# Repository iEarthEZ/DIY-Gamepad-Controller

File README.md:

# DIY-Gamepad-Controller
Making a custom gamepad controller from scratch. {I'll update code files and firmware when my parts get shipped.}.

Lets walk you through here from where i got the idea to where we are now. First things first the idea came to my mind because not too long ago i bought my cool red ps4 controller so i thought "what if i could make something like this myself?". Thats what it hit me, i was like I can make that so i got to work on the research my brother was making a split keyboard and he used the arduino pro micro mini as the "brain" or main chip. He said if you are making something like that use the pro micro mini so i atlast settled down with the normal usb-c version of the pro micro(the mini's pins are abit different). If you are making this project like me i recommend the video https://www.youtube.com/watch?v=mvv1BRjswew by Voltaat. It will get you started with ide and programming so it'll be easy and i recommend watching some soldering tutorials lol. Also first things first you should download all the project files and open them up in kicad and check it out or edit stuff yourself!(feel free). If you goto the pcb section and press alt + 3 you can see a base model of how it will look(its the reference image at the start of this readme). Its straight forward, upload gerber files to jlcpcb or pcbway or anyother you like i guess, wait for the pcb to get shipped to you, order the given parts in the BOM and just assemble them. Thats it! I made the controller a basic comfortable shape but you can make it any shape you like. If you know the basics of kicad i don't think it will be a pain to get through everything. It was my second ever pcb and project with kicad and stuff so i was pretty scared but at the end i found out it ain't hard. Looking forward to everyone that makes this project and in the next upd i'll drop all the firmware and code files even a tutorial on how to code the ide after my parts gets shipped. Till then. Peace.

HERE IS THE BOM!!!!! (NOTE THAT ALL OF THIS IS FROM MY INSIDE COUNTRY'S WEBSITES YOU CAN JUST SEARCH FOR THE PART NAMES AND GET THEM FROM YOUR LOCAL SHOP OR LOCAL WEBSITE)

|Name                                                                                                                                                                  |Purpose                                                                            |Quantity|Total Cost (USD)|Link                                                                                                                                                                                                                                                                                                                                                                                                                                                                                                                                                                                                                                                                                                                                                                                                                                                                                                                                                                                                                                                                                                   |Distributor|
|----------------------------------------------------------------------------------------------------------------------------------------------------------------------|-----------------------------------------------------------------------------------|--------|----------------|-------------------------------------------------------------------------------------------------------------------------------------------------------------------------------------------------------------------------------------------------------------------------------------------------------------------------------------------------------------------------------------------------------------------------------------------------------------------------------------------------------------------------------------------------------------------------------------------------------------------------------------------------------------------------------------------------------------------------------------------------------------------------------------------------------------------------------------------------------------------------------------------------------------------------------------------------------------------------------------------------------------------------------------------------------------------------------------------------------|-----------|
|Joystick Dual Axis 5 Pin Breakout Module For Arduino                                                                                                                  |Joysticks for the controller                                                       |2       |1.61            |https://www.bdtronics.com/joystick-dual-axis-5-pin-breakout-module-for-arduino.html                                                                                                                                                                                                                                                                                                                                                                                                                                                                                                                                                                                                                                                                                                                                                                                                                                                                                                                                                                                                                    |BDTronics  |
|10Pcs- RIGHT Angle Momentary 2Pin Tactile Tact Push Button Switches 2 Pin 6x6x7mm 90 Degree Bend On Off PCB DIP Through Hole Touch Switch Momentary Push Button Switch|right angled buttons for the shoulder and triggers                                 |1       |0.76            |https://www.daraz.com.bd/products/10-2-2-6x6x7mm-90-pcb-i129768178-s1049544950.html?c=&channelLpJumpArgs=&clickTrackInfo=query%253Aangled%252Bpush%252Bbutton%253Bnid%253A129768178%253Bsrc%253ALazadaMainSrp%253Brn%253A0ec6cdb791f19f113f57f372a77d82df%253Bregion%253Abd%253Bsku%253A129768178_BD%253Bprice%253A93%253Bclient%253Adesktop%253Bsupplier_id%253A1000750%253Bsession_id%253A%253Bbiz_source%253Ah5_external%253Bslot%253A13%253Butlog_bucket_id%253A470687%253Basc_category_id%253A10000486%253Bitem_id%253A129768178%253Bsku_id%253A1049544950%253Bshop_id%253A6947%253BtemplateInfo%253A&freeshipping=0&fs_ab=1&fuse_fs=&lang=en&location=Dhaka&price=93&priceCompare=skuId%3A1049544950%3Bsource%3Alazada-search-voucher%3Bsn%3A0ec6cdb791f19f113f57f372a77d82df%3BoriginPrice%3A9300%3BdisplayPrice%3A9300%3BsinglePromotionId%3A-1%3BsingleToolCode%3AmockedSalePrice%3BvoucherPricePlugin%3A0%3Btimestamp%3A1777640799160&ratingscore=4.666666666666667&request_id=0ec6cdb791f19f113f57f372a77d82df&review=15&sale=70&search=1&source=search&spm=a2a0e.searchlist.list.13&stock=1|DarazBD    |
|Mini Push Button Tactile Switch 4 Pin (6mm*6mm*4.5mm)                                                                                                                 |buttons of the controller                                                          |10      |0.41            |https://www.bdtronics.com/mini-push-button-tactile-switch-4-pin-6mm-6mm-4-5mm.html                                                                                                                                                                                                                                                                                                                                                                                                                                                                                                                                                                                                                                                                                                                                                                                                                                                                                                                                                                                                                     |BDTronics  |
|1/4 Resistor                                                                                                                                                          |resistor so the led doesn't burn out                                               |1       |0.02            |https://www.bdtronics.com/carbon-film-1-4w-resistor.html                                                                                                                                                                                                                                                                                                                                                                                                                                                                                                                                                                                                                                                                                                                                                                                                                                                                                                                                                                                                                                               |BDTronics  |
|WHITE LED                                                                                                                                                             |showing connection status of the controller and white led on black pcb is just good|1       |0.02            |https://www.bdtronics.com/3mm-led-red-green-blue-yellow-white.html                                                                                                                                                                                                                                                                                                                                                                                                                                                                                                                                                                                                                                                                                                                                                                                                                                                                                                                                                                                                                                     |BDTronics  |
|Arduino Pro Micro                                                                                                                                                     |the brain of this controller                                                       |1       |5.05            |https://www.bdtronics.com/arduino-pro-micro-atmega32u4-5v-16mhz.html                                                                                                                                                                                                                                                                                                                                                                                                                                                                                                                                                                                                                                                                                                                                                                                                                                                                                                                                                                                                                                   |BDTronics  |
|PCB                                                                                                                                                                   |the pcb                                                                            |1       |15.50           |https://trade.jlcpcb.com/checkout/payMethod/?unionSettleId=26dcc378283c4002b6bfed6f815bbe98&systemType=order_pcb&orderTypes=order_pcb&calType=PRE_CAL&couponDemo=1&spm=Jlcpcb.Partcart.1002                                                                                                                                                                                                                                                                                                                                                                                                                                                                                                                                                                                                                                                                                                                                                                                                                                                                                                            |JLCPCB     |

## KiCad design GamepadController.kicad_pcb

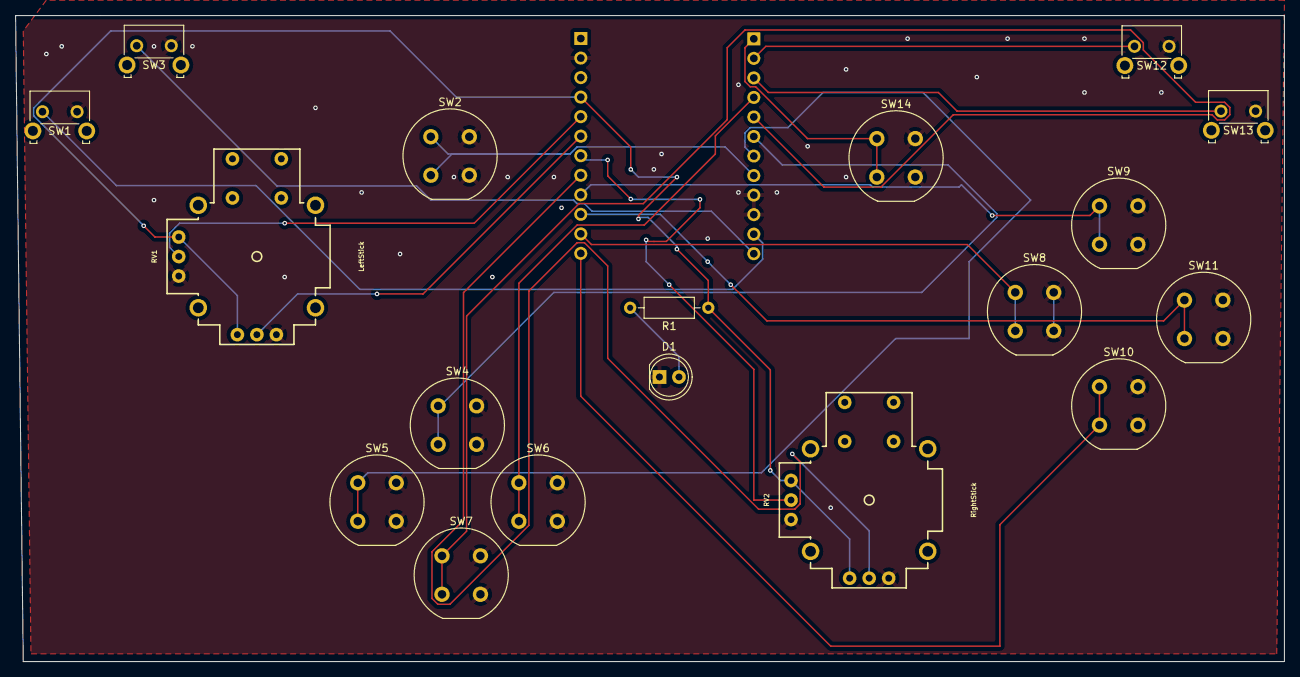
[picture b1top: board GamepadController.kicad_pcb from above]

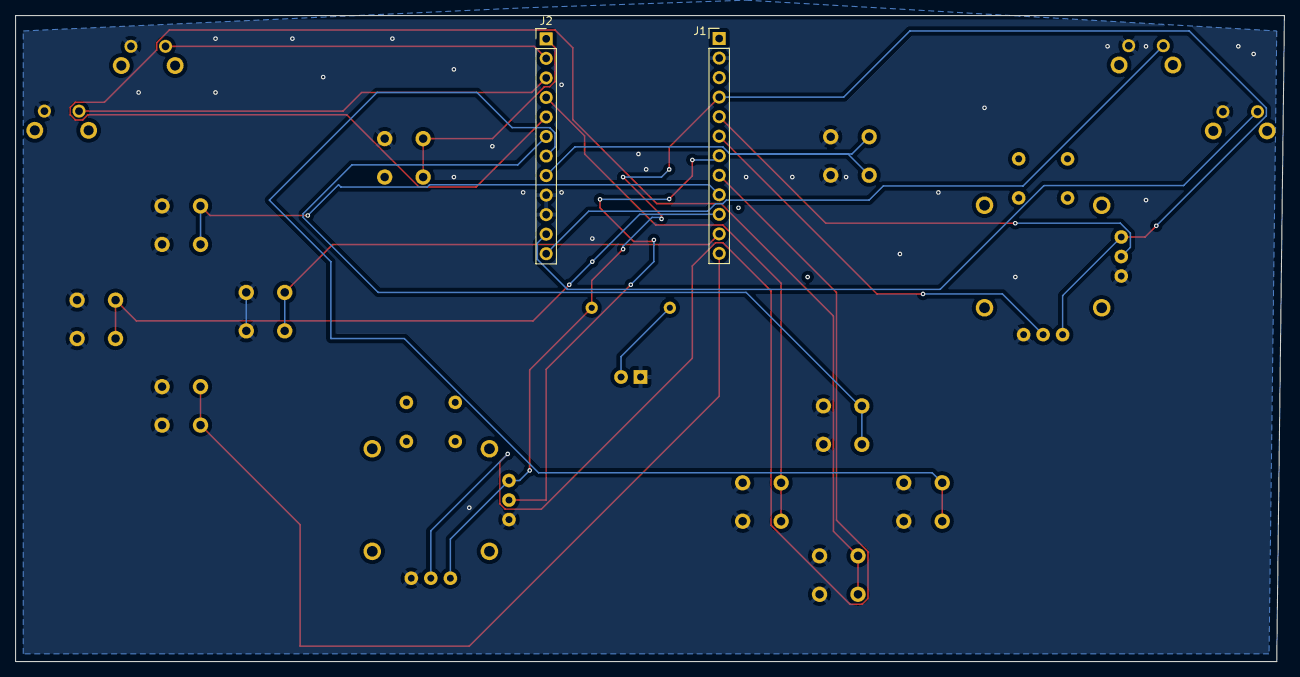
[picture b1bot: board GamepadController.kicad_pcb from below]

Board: 2 copper layers, 165.0 x 84.0 mm, 20 parts (2 on the bottom side), 21 nets.

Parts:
D1: LED; LED_D5.0mm
J1, J2: Conn_01x12_Pin; PinHeader_1x12_P2.54mm_Vertical
R1: R; R_Axial_DIN0207_L6.3mm_D2.5mm_P10.16mm_Horizontal
RV1: LeftStick; Joystick
RV2: RightStick; Joystick
SW1: LeftButton; SW_Tactile_SKHH_Angled
SW2, SW14: BackButton; Push_E-Switch_KS01Q01
SW3: LeftTrigger; SW_Tactile_SKHH_Angled
SW4: Up; Push_E-Switch_KS01Q01
SW5: Left; Push_E-Switch_KS01Q01
SW6: Right; Push_E-Switch_KS01Q01
SW7: Down; Push_E-Switch_KS01Q01
SW8: X; Push_E-Switch_KS01Q01
SW9: Y; Push_E-Switch_KS01Q01
SW10: A; Push_E-Switch_KS01Q01
SW11: B; Push_E-Switch_KS01Q01
SW12: RightTrigger; SW_Tactile_SKHH_Angled
SW13: RightButton; SW_Tactile_SKHH_Angled

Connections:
/A0: J1.8, RV2.5
/A1: J1.7, RV2.2
/A2: J1.6, RV1.5
/A3: J1.5, RV1.2
/D0: J2.12, SW3.1
/D1: J2.11, SW1.1
/D2: J2.8, SW2.1, SW2.3
/D3: J2.7, SW5.1, SW5.3
/D4: J2.6, SW4.1, SW4.3
/D5: J2.5, SW7.1, SW7.3
/D6: J2.4, SW6.1, SW6.3
/D7: J2.3, SW13.1
/D8: J2.2, SW12.1
/D9: J2.1, SW14.1, SW14.3
/D10: J1.12, SW10.1, SW10.3
/D14: J1.10, SW11.1, SW11.3
/D15: J1.9, SW9.1, SW9.3
/D16: J1.11, SW8.1, SW8.3
/GND: D1.1 (K), J1.2, J2.9, J2.10, RV1.3, RV1.6, RV2.3, RV2.6, SW1.2, SW2.2, SW2.4, SW3.2, SW4.2, SW4.4, SW5.2, SW5.4, SW6.2, SW6.4, SW7.2, SW7.4, SW8.2, SW8.4, SW9.2, SW9.4, SW10.2, SW10.4, SW11.2, SW11.4, SW12.2, SW13.2, SW14.2, SW14.4
/VCC: J1.4, R1.1, RV1.1, RV1.4, RV2.1, RV2.4
unnamed: D1.2 (A), R1.2
